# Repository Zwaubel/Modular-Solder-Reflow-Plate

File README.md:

# **Modular Solder Reflow Plate**

This project is based on [AfterEarthLTD/Solder-Reflow-Plate](https://github.com/AfterEarthLTD/Solder-Reflow-Plate) and [Johboh/Solder-Reflow-Plate](https://github.com/Johboh/Solder-Reflow-Plate)! Check out their repositories for more information.

> **⚠️ Attention:**  
> This project is currently under development and not fully tested. Building and using this project is not recommended at this time.

Changes compard to AfterEarthLTD's and Johboh's versions:
- revised main control board
  - mcu: ESP32 S3 using the WROOM module (BT and Wifi capable)
  - input voltage monitoring capabilities
  - revised component layout
  - I2C OLED display and 4-button-input
  - beeper
  - SD-Card-Reader
 
## Disclaimer
We are dealing with heat and high current here. Use at your own risk! Don't leave solder plate unattended.

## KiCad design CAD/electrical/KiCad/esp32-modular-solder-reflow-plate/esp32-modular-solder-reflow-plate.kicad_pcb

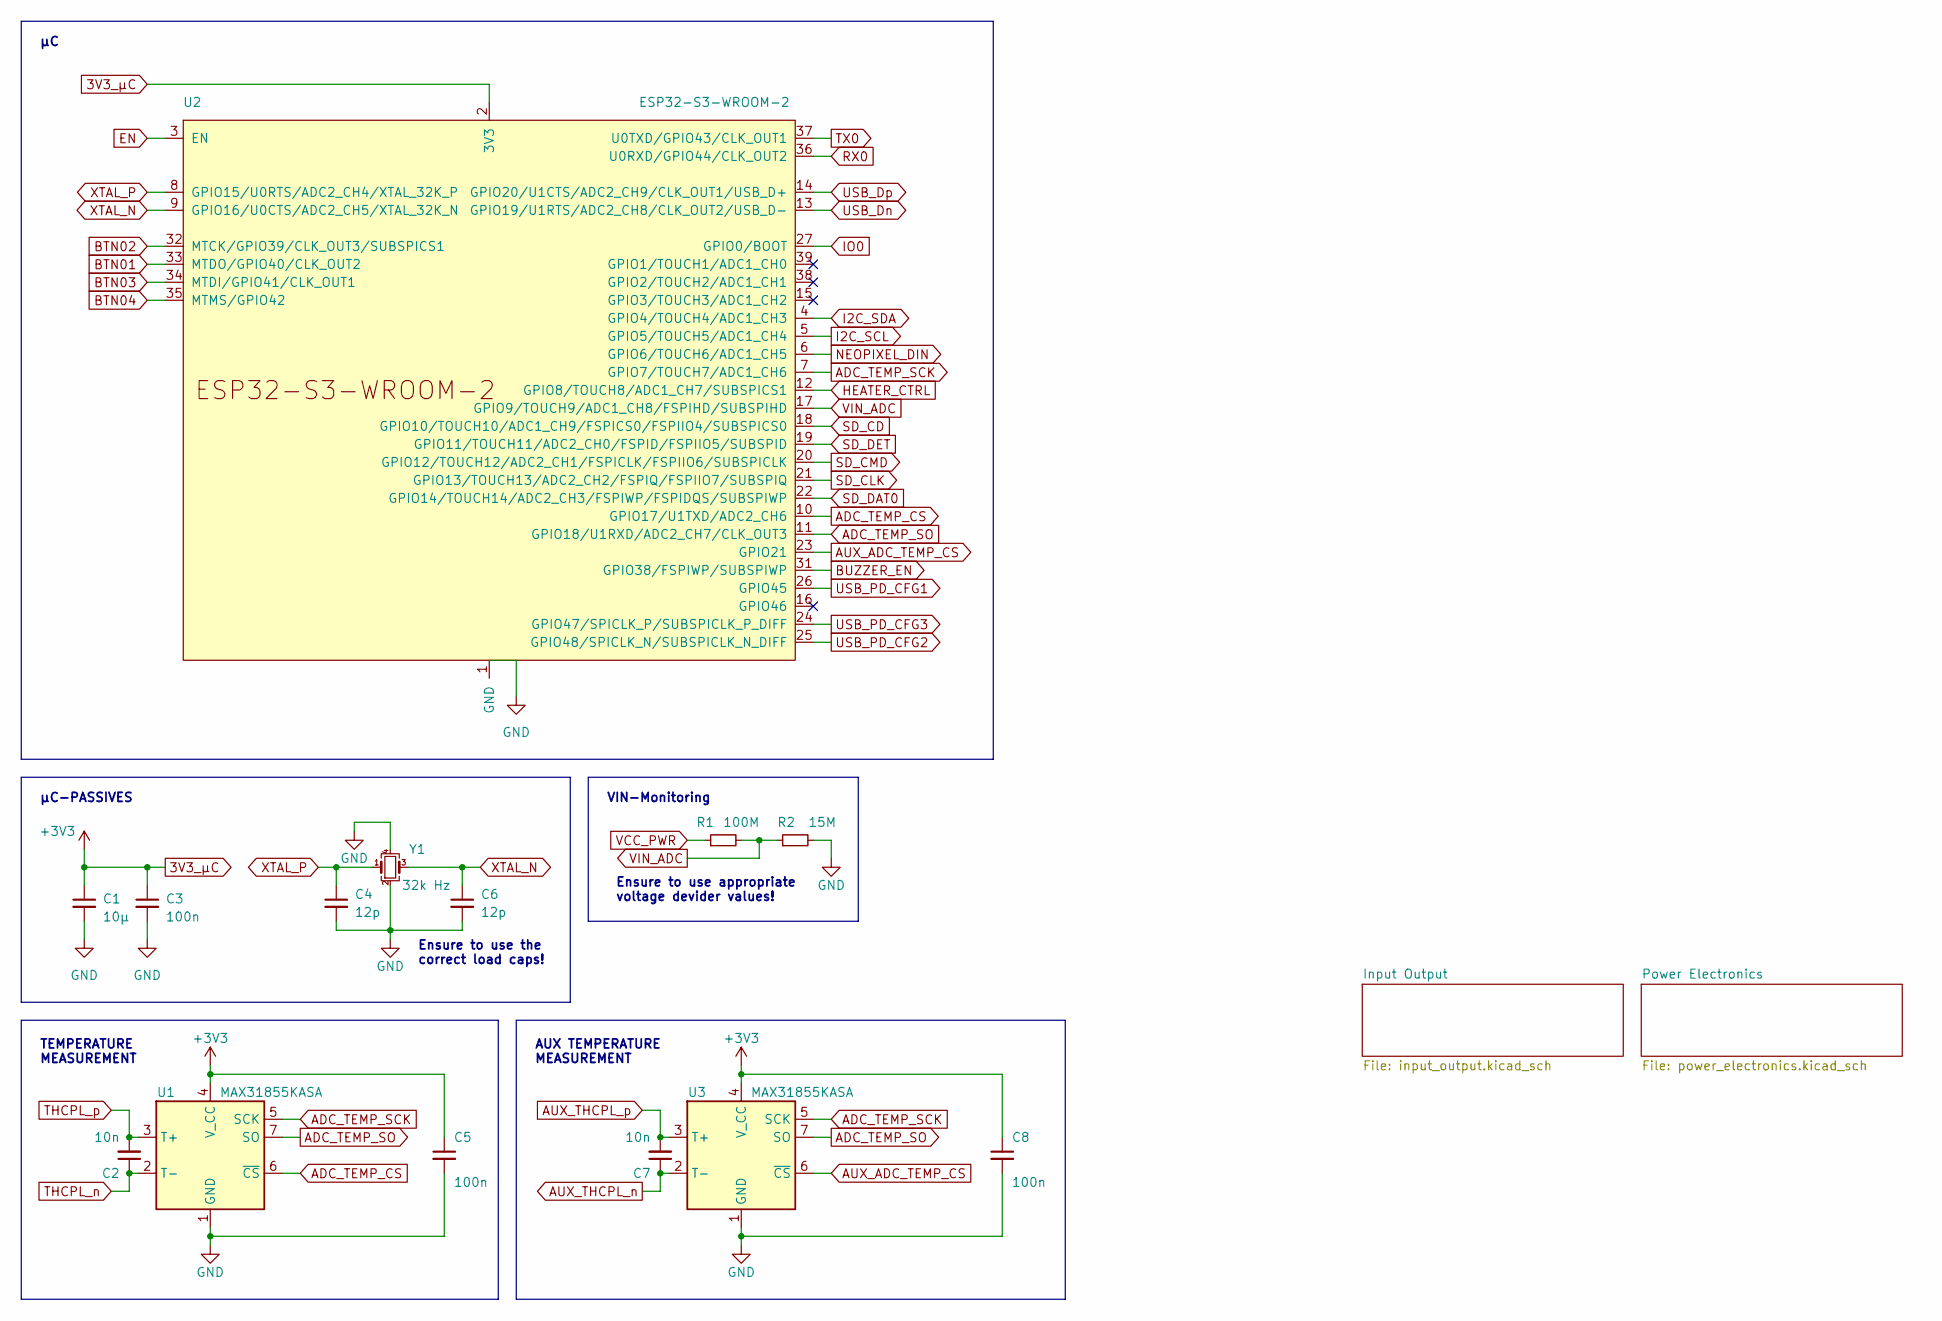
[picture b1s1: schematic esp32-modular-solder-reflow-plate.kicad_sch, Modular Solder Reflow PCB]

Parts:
C1: 10µ; C_0603_1608Metric_Pad1.08x0.95mm_HandSolder
C2, C7: 10n; C_0603_1608Metric_Pad1.08x0.95mm_HandSolder
C3, C5, C8: 100n; C_0603_1608Metric_Pad1.08x0.95mm_HandSolder
C4, C6: 12p; C_0603_1608Metric_Pad1.08x0.95mm_HandSolder
R1: 100M; R_0603_1608Metric_Pad0.98x0.95mm_HandSolder
R2: 15M; R_0603_1608Metric_Pad0.98x0.95mm_HandSolder
U1, U3: MAX31855KASA; SOIC-8_3.9x4.9mm_P1.27mm
U2: ESP32-S3-WROOM-2
Y1: 32k Hz; Crystal_SMD_3225-4Pin_3.2x2.5mm_HandSoldering

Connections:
3V3_µC: C1.1, C3.1, C5.1, C8.1, U1.4 (V_CC), U2.2 (3V3), U3.4 (V_CC); also elsewhere on the board
ADC_TEMP_CS: U1.6 (~CS), U2.10 (GPIO17/U1TXD/ADC2_CH6)
ADC_TEMP_SCK: U1.5 (SCK), U2.7 (GPIO7/TOUCH7/ADC1_CH6), U3.5 (SCK)
ADC_TEMP_SO: U1.7 (SO), U2.11 (GPIO18/U1RXD/ADC2_CH7/CLK_OUT3), U3.7 (SO)
AUX_ADC_TEMP_CS: U2.23 (GPIO21), U3.6 (~CS)
AUX_THCPL_n: C7.1, U3.2 (T-); also elsewhere on the board
AUX_THCPL_p: C7.2, U3.3 (T+); also elsewhere on the board
BTN01: U2.33 (MTDO/GPIO40/CLK_OUT2); also elsewhere on the board
BTN02: U2.32 (MTCK/GPIO39/CLK_OUT3/SUBSPICS1); also elsewhere on the board
BTN03: U2.34 (MTDI/GPIO41/CLK_OUT1); also elsewhere on the board
BTN04: U2.35 (MTMS/GPIO42); also elsewhere on the board
BUZZER_EN: U2.31 (GPIO38/FSPIWP/SUBSPIWP); also elsewhere on the board
EN: U2.3 (EN); also elsewhere on the board
HEATER_CTRL: U2.12 (GPIO8/TOUCH8/ADC1_CH7/SUBSPICS1); also elsewhere on the board
HEATER_P: R1.1; also elsewhere on the board
I2C_SCL: U2.5 (GPIO5/TOUCH5/ADC1_CH4); also elsewhere on the board
I2C_SDA: U2.4 (GPIO4/TOUCH4/ADC1_CH3); also elsewhere on the board
IO0: U2.27 (GPIO0/BOOT); also elsewhere on the board
NEOPIXEL_DIN: U2.6 (GPIO6/TOUCH6/ADC1_CH5); also elsewhere on the board
PWR_IN_N: C1.2, C3.2, C4.2, C5.2, C6.2, C8.2, R2.2, U1.1 (GND), U2.1 (GND), U2.40 (GND), U2.41 (GND), U3.1 (GND), Y1.2, Y1.4; also elsewhere on the board
RX0: U2.36 (U0RXD/GPIO44/CLK_OUT2); also elsewhere on the board
SD_CD: U2.18 (GPIO10/TOUCH10/ADC1_CH9/FSPICS0/FSPIIO4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); also elsewhere on the board
SD_CLK: U2.21 (GPIO13/TOUCH13/ADC2_CH2/FSPIQ/FSPIIO7/S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); also elsewhere on the board
SD_CMD: U2.20 (GPIO12/TOUCH12/ADC2_CH1/FSPICLK/FSPIIO6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); also elsewhere on the board
SD_DAT0: U2.22 (GPIO14/TOUCH14/ADC2_CH3/FSPIWP/FSPIDQS/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); also elsewhere on the board
SD_DET: U2.19 (GPIO11/TOUCH11/ADC2_CH0/FSPID/FSPIIO5/S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); also elsewhere on the board
THCPL_n: C2.1, U1.2 (T-); also elsewhere on the board
THCPL_p: C2.2, U1.3 (T+); also elsewhere on the board
TX0: U2.37 (U0TXD/GPIO43/CLK_OUT1); also elsewhere on the board
USB_Dn: U2.13 (GPIO19/U1RTS/ADC2_CH8/CLK_OUT2/USB_D-); also elsewhere on the board
USB_Dp: U2.14 (GPIO20/U1CTS/ADC2_CH9/CLK_OUT1/USB_D+); also elsewhere on the board
USB_PD_CFG1: U2.26 (GPIO45); also elsewhere on the board
USB_PD_CFG2: U2.25 (GPIO48/SPICLK_N/SUBSPICLK_N_DIFF); also elsewhere on the board
USB_PD_CFG3: U2.24 (GPIO47/SPICLK_P/SUBSPICLK_P_DIFF); also elsewhere on the board
VIN_ADC: R1.2, R2.1, U2.17 (GPIO9/TOUCH9/ADC1_CH8/FSPIHD/SUBSPIHD)
XTAL_N: C6.1, U2.9 (GPIO16/U0CTS/ADC2_CH5/XTAL_32K_N), Y1.3
XTAL_P: C4.1, U2.8 (GPIO15/U0RTS/ADC2_CH4/XTAL_32K_P), Y1.1

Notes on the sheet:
Ensure to use the correct load caps!
TEMPERATURE MEASUREMENT
Ensure to use appropriate voltage devider values!
µC-PASSIVES
VIN-Monitoring
AUX TEMPERATURE MEASUREMENT

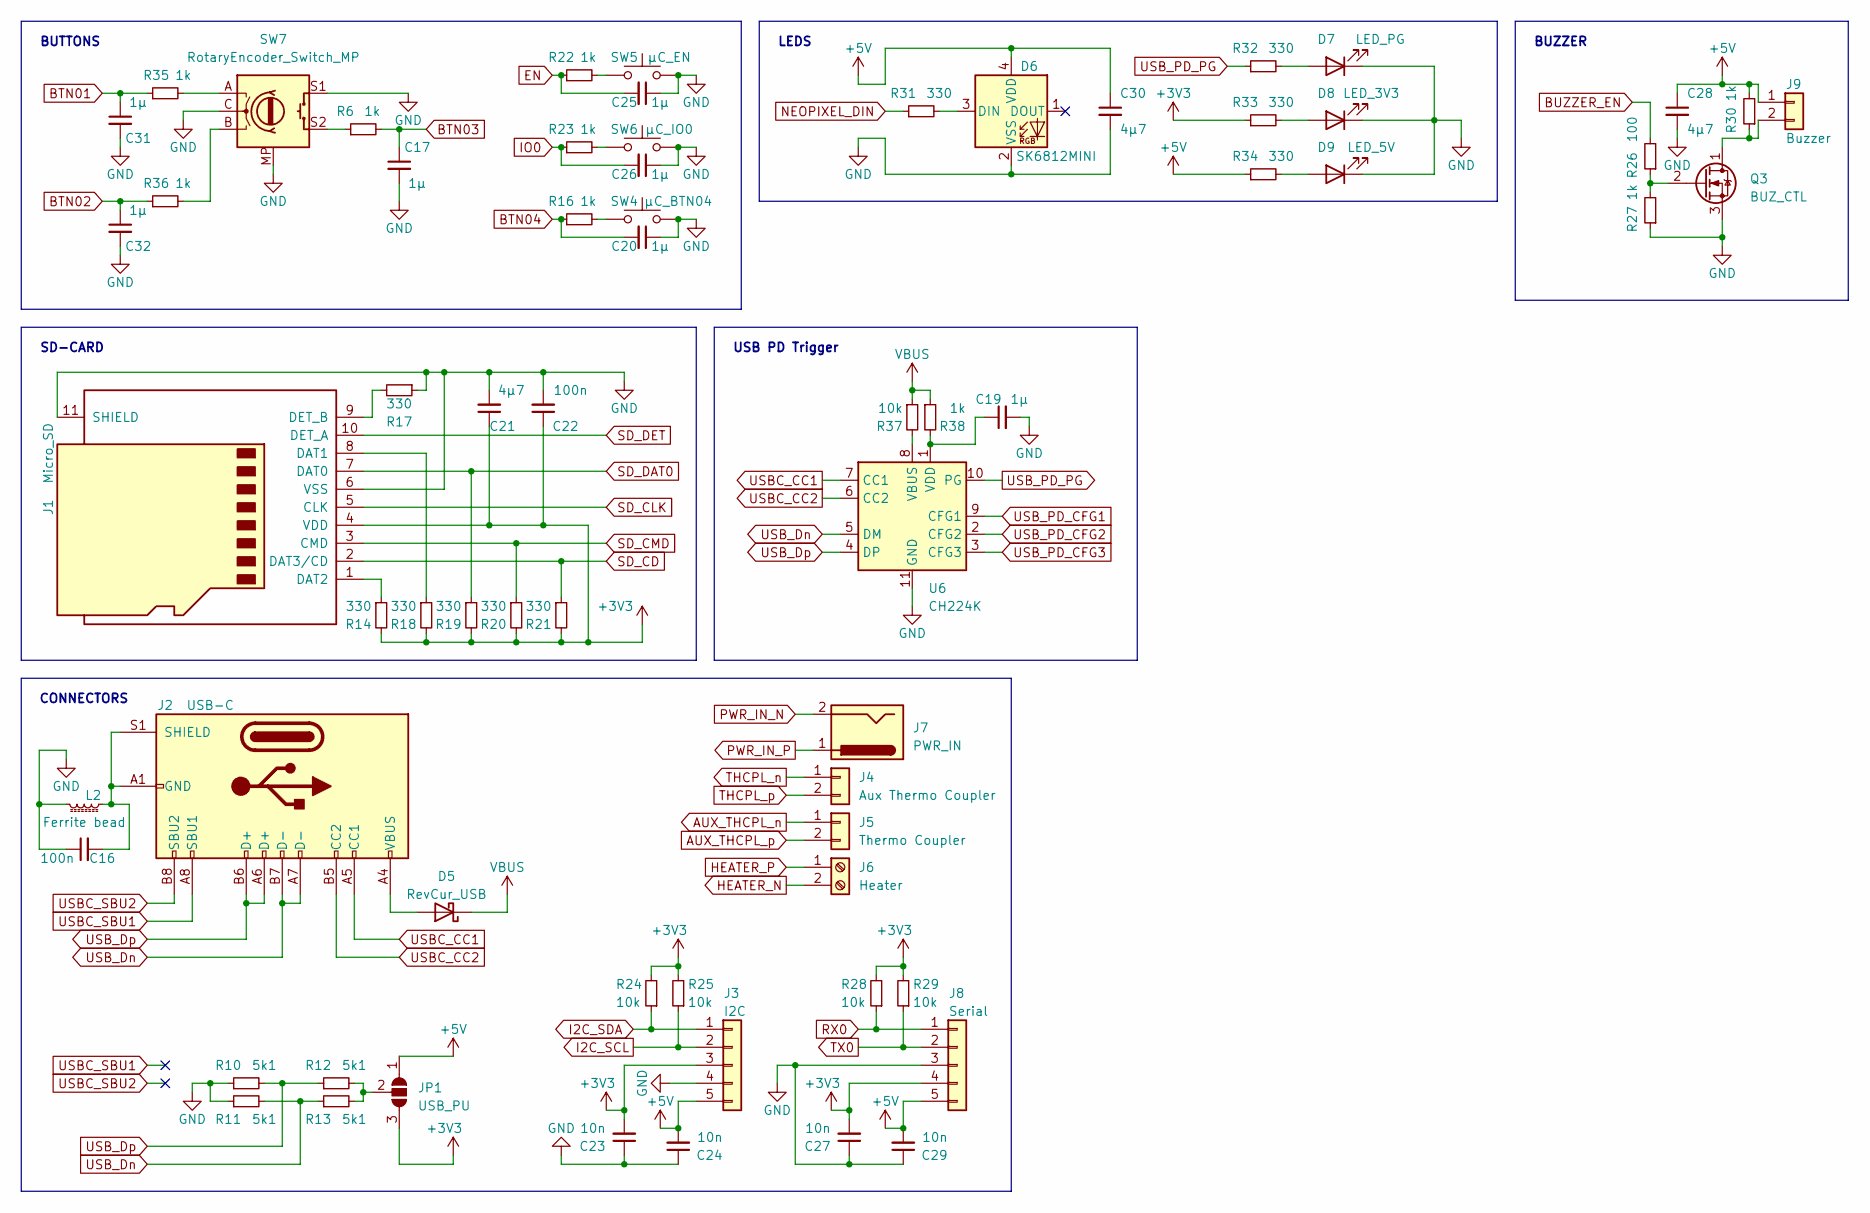
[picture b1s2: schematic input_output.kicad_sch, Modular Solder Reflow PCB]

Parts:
C16, C22: 100n; C_0603_1608Metric_Pad1.08x0.95mm_HandSolder
C17, C19, C20, C25, C26, C31, C32: 1µ; C_0603_1608Metric_Pad1.08x0.95mm_HandSolder
C21, C28, C30: 4µ7; C_0603_1608Metric_Pad1.08x0.95mm_HandSolder
C23, C24, C27, C29: 10n; C_0603_1608Metric_Pad1.08x0.95mm_HandSolder
D5: RevCur_USB; D_1210_3225Metric_Pad1.42x2.65mm_HandSolder
D6: SK6812MINI; LED_SK6812MINI_PLCC4_3.5x3.5mm_P1.75mm
D7: LED_PG; LED_0603_1608Metric_Pad1.05x0.95mm_HandSolder
D8: LED_3V3; LED_0603_1608Metric_Pad1.05x0.95mm_HandSolder
D9: LED_5V; LED_0603_1608Metric_Pad1.05x0.95mm_HandSolder
J1: Micro_SD; microSD_HC_Hirose_DM3D-SF
J2: USB-C; USB_C_Receptacle_G-Switch_GT-USB-7010ASV
J3: I2C; PinSocket_1x05_P2.54mm_Vertical
J4: Aux Thermo Coupler; JST_XH_B2B-XH-A_1x02_P2.50mm_Vertical
J5: Thermo Coupler; JST_XH_B2B-XH-A_1x02_P2.50mm_Vertical
J6: Heater; TerminalBlock_bornier-2_P5.08mm
J7: PWR_IN; BarrelJack_CUI_PJ-063AH_Horizontal
J8: Serial; PinSocket_1x05_P2.54mm_Vertical
J9: Buzzer; JST_XH_B2B-XH-A_1x02_P2.50mm_Vertical
JP1: USB_PU; SolderJumper-3_P1.3mm_Open_RoundedPad1.0x1.5mm
L2: Ferrite bead; L_0603_1608Metric_Pad1.05x0.95mm_HandSolder
Q3: BUZ_CTL; SOT-23
R6, R16, R22, R23, R27, R30, R35, R36, R38: 1k; R_0603_1608Metric_Pad0.98x0.95mm_HandSolder
R10, R11, R12, R13: 5k1; R_0603_1608Metric_Pad0.98x0.95mm_HandSolder
R14, R17, R18, R19, R20, R21, R31, R32, R33, R34: 330; R_0603_1608Metric_Pad0.98x0.95mm_HandSolder
R24, R25, R28, R29, R37: 10k; R_0603_1608Metric_Pad0.98x0.95mm_HandSolder
R26: 100; R_0603_1608Metric_Pad0.98x0.95mm_HandSolder
SW4: µC_BTN04; SW_PUSH_6mm
SW5: µC_EN; SW_Tactile_SKHH_Angled
SW6: µC_IO0; SW_Tactile_SKHH_Angled
SW7: RotaryEncoder_Switch_MP; RotaryEncoder_Alps_EC11E-Switch_Vertical_H20mm
U6: CH224K; SSOP-10-1EP_3.9x4.9mm_P1mm_EP2.1x3.3mm

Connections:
3V3_µC: C21.1, C22.1, C23.2, C27.2, J1.4 (VDD), J3.3, J8.4, JP1.3 (B), R14.2, R18.2, R19.2, R20.2, R21.2, R24.2, R25.2, R28.2, R29.2, R33.1; also elsewhere on the board
+5V: C24.2, C28.1, C29.2, C30.1, D6.4 (VDD), J3.5, J8.5, J9.1, JP1.1 (A), R30.2, R34.1; also elsewhere on the board
AUX_THCPL_n: J5.1; also elsewhere on the board
AUX_THCPL_p: J5.2; also elsewhere on the board
BTN01: C31.1, R35.1; also elsewhere on the board
BTN02: C32.1, R36.1; also elsewhere on the board
BTN03: C17.1, R6.2; also elsewhere on the board
BTN04: C20.2, R16.1; also elsewhere on the board
BUZZER_EN: R26.2; also elsewhere on the board
EN: C25.2, R22.1; also elsewhere on the board
HEATER_N: J6.2; also elsewhere on the board
HEATER_P: J6.1; also elsewhere on the board
I2C_SCL: J3.2, R25.1; also elsewhere on the board
I2C_SDA: J3.1, R24.1; also elsewhere on the board
IO0: C26.2, R23.1; also elsewhere on the board
NEOPIXEL_DIN: R31.1; also elsewhere on the board
unnamed: D5.2 (A), J2.A4 (VBUS), J2.A9 (VBUS), J2.B4 (VBUS), J2.B9 (VBUS)
unnamed: D6.3 (DIN), R31.2
unnamed: D7.2 (A), R32.2
unnamed: D8.2 (A), R33.2
unnamed: D9.2 (A), R34.2
unnamed: J1.8 (DAT1), R18.1
unnamed: J1.1 (DAT2), R14.1
unnamed: J1.9 (DET_B), R17.2
unnamed: C16.2, J2.A1 (GND), J2.A12 (GND), J2.B1 (GND), J2.B12 (GND), J2.S1 (SHIELD), L2.1
unnamed: J9.2, Q3.1 (D), R30.1
unnamed: JP1.2 (C), R12.2, R13.2
unnamed: Q3.2 (G), R26.1, R27.2
unnamed: R6.1, SW7.S2
unnamed: R16.2, SW4.1
unnamed: R22.2, SW5.1
unnamed: R23.2, SW6.1
unnamed: R35.2, SW7.A
unnamed: R36.2, SW7.B
unnamed: R37.2, U6.8 (VBUS)
unnamed: C19.1, R38.2, U6.1 (VDD)
PWR_IN_N: C16.1, C17.2, C19.2, C20.1, C21.2, C22.2, C23.1, C24.1, C25.1, C26.1, C27.1, C28.2, C29.1, C30.2, C31.2, C32.2, D6.2 (VSS), D7.1 (K), D8.1 (K), D9.1 (K), J1.6 (VSS), J1.11 (SHIELD), J3.4, J7.2, J8.3, L2.2, Q3.3 (S), R10.1, R11.1, R17.1, R27.1, SW4.2, SW5.2, SW6.2, SW7.C, SW7.MP, SW7.S1, U6.11 (GND); also elsewhere on the board
PWR_IN_P: J7.1; also elsewhere on the board
RX0: J8.1, R28.1; also elsewhere on the board
SD_CD: J1.2 (DAT3/CD), R21.1; also elsewhere on the board
SD_CLK: J1.5 (CLK); also elsewhere on the board
SD_CMD: J1.3 (CMD), R20.1; also elsewhere on the board
SD_DAT0: J1.7 (DAT0), R19.1; also elsewhere on the board
SD_DET: J1.10 (DET_A); also elsewhere on the board
THCPL_n: J4.1; also elsewhere on the board
THCPL_p: J4.2; also elsewhere on the board
TX0: J8.2, R29.1; also elsewhere on the board
USBC_CC1: J2.A5 (CC1), U6.7 (CC1)
USBC_CC2: J2.B5 (CC2), U6.6 (CC2)
USBC_SBU1: J2.A8 (SBU1)
USBC_SBU2: J2.B8 (SBU2)
USB_Dn: J2.A7 (D-), J2.B7 (D-), R11.2, R13.1, U6.5 (DM); also elsewhere on the board
USB_Dp: J2.A6 (D+), J2.B6 (D+), R10.2, R12.1, U6.4 (DP); also elsewhere on the board
USB_PD_CFG1: U6.9 (CFG1); also elsewhere on the board
USB_PD_CFG2: U6.2 (CFG2); also elsewhere on the board
USB_PD_CFG3: U6.3 (CFG3); also elsewhere on the board
USB_PD_PG: R32.1, U6.10 (PG)
VDD: D5.1 (K), R37.1, R38.1; also elsewhere on the board

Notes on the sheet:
BUZZER
BUTTONS
SD-CARD
CONNECTORS
LEDS
USB PD Trigger

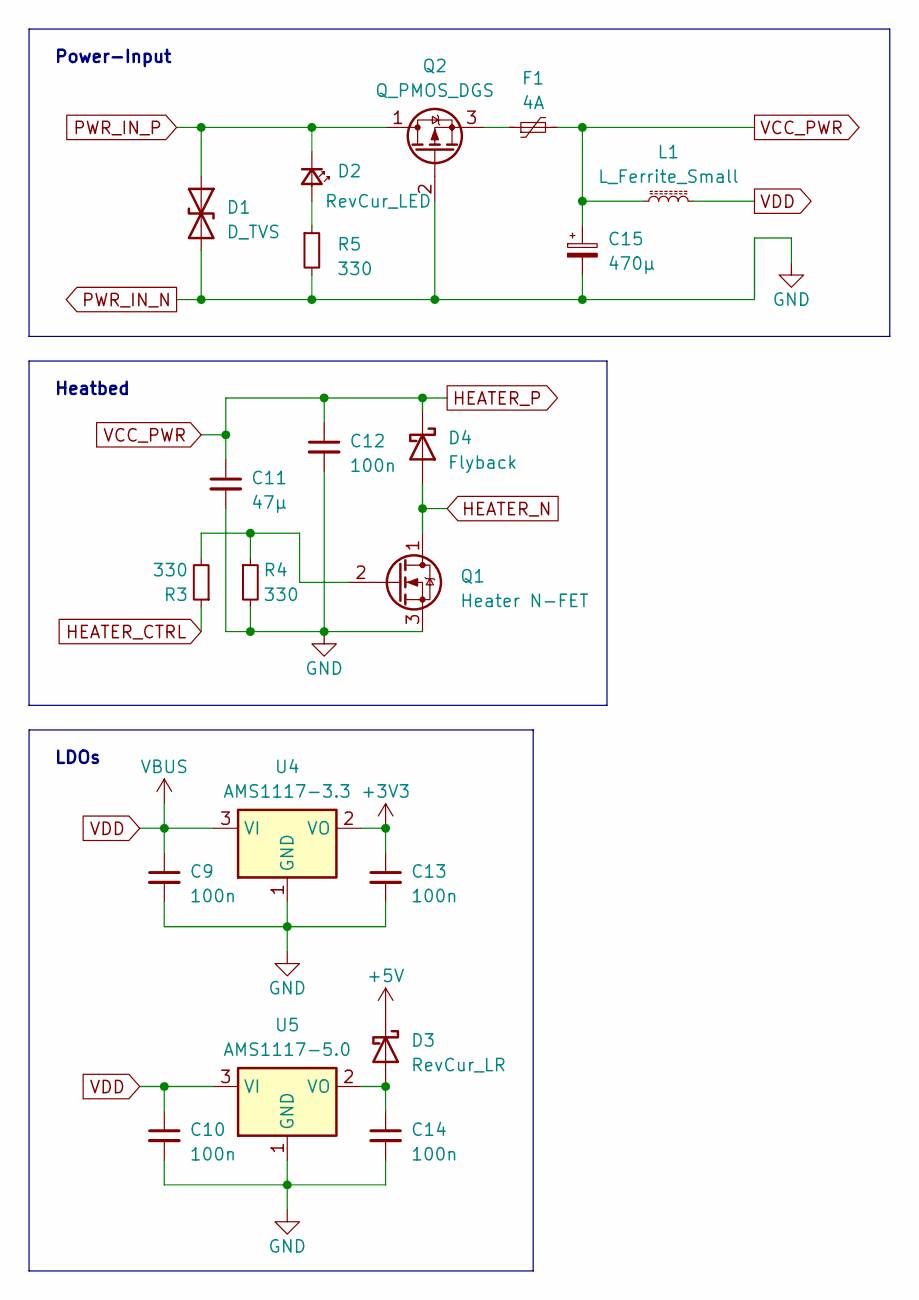
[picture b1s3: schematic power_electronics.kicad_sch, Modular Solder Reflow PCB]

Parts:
C9, C10, C12, C13, C14: 100n; C_0603_1608Metric_Pad1.08x0.95mm_HandSolder
C11: 47µ; C_0603_1608Metric_Pad1.08x0.95mm_HandSolder
C15: 470µ; CP_Radial_D6.3mm_P2.50mm
D1: D_TVS; D_0603_1608Metric_Pad1.05x0.95mm_HandSolder
D2: RevCur_LED; LED_0603_1608Metric_Pad1.05x0.95mm_HandSolder
D3: RevCur_LR; D_1210_3225Metric_Pad1.42x2.65mm_HandSolder
D4: Flyback; D_1210_3225Metric_Pad1.42x2.65mm_HandSolder
F1: 4A; Fuse_BelFuse_0ZRE0005FF_L8.3mm_W3.8mm
L1: L_Ferrite_Small; L_0805_2012Metric_Pad1.15x1.40mm_HandSolder
Q1: Heater N-FET; ATPAK-2
Q2: Q_PMOS_DGS; ATPAK-2
R3, R4, R5: 330; R_0603_1608Metric_Pad0.98x0.95mm_HandSolder
U4: AMS1117-3.3; SOT-223-3_TabPin2
U5: AMS1117-5.0; SOT-223-3_TabPin2

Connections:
3V3_µC: C13.1, U4.2 (VO); also elsewhere on the board
+5V: D3.1 (K); also elsewhere on the board
HEATER_CTRL: R3.1; also elsewhere on the board
HEATER_N: D4.2 (A), Q1.1 (D); also elsewhere on the board
HEATER_P: C11.1, C12.1, C15.1, D4.1 (K), F1.2, L1.1; also elsewhere on the board
unnamed: D2.2 (A), R5.1
unnamed: C14.1, D3.2 (A), U5.2 (VO)
unnamed: Q1.2 (G), R3.2, R4.1
unnamed: F1.1, Q2.3 (S)
PWR_IN_N: C9.2, C10.2, C11.2, C12.2, C13.2, C14.2, C15.2, D1.2 (A2), Q1.3 (S), Q2.2 (G), R4.2, R5.2, U4.1 (GND), U5.1 (GND); also elsewhere on the board
PWR_IN_P: D1.1 (A1), D2.1 (K), Q2.1 (D); also elsewhere on the board
VDD: C9.1, C10.1, L1.2, U4.3 (VI), U5.3 (VI); also elsewhere on the board

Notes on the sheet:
Power-Input
Heatbed
LDOs

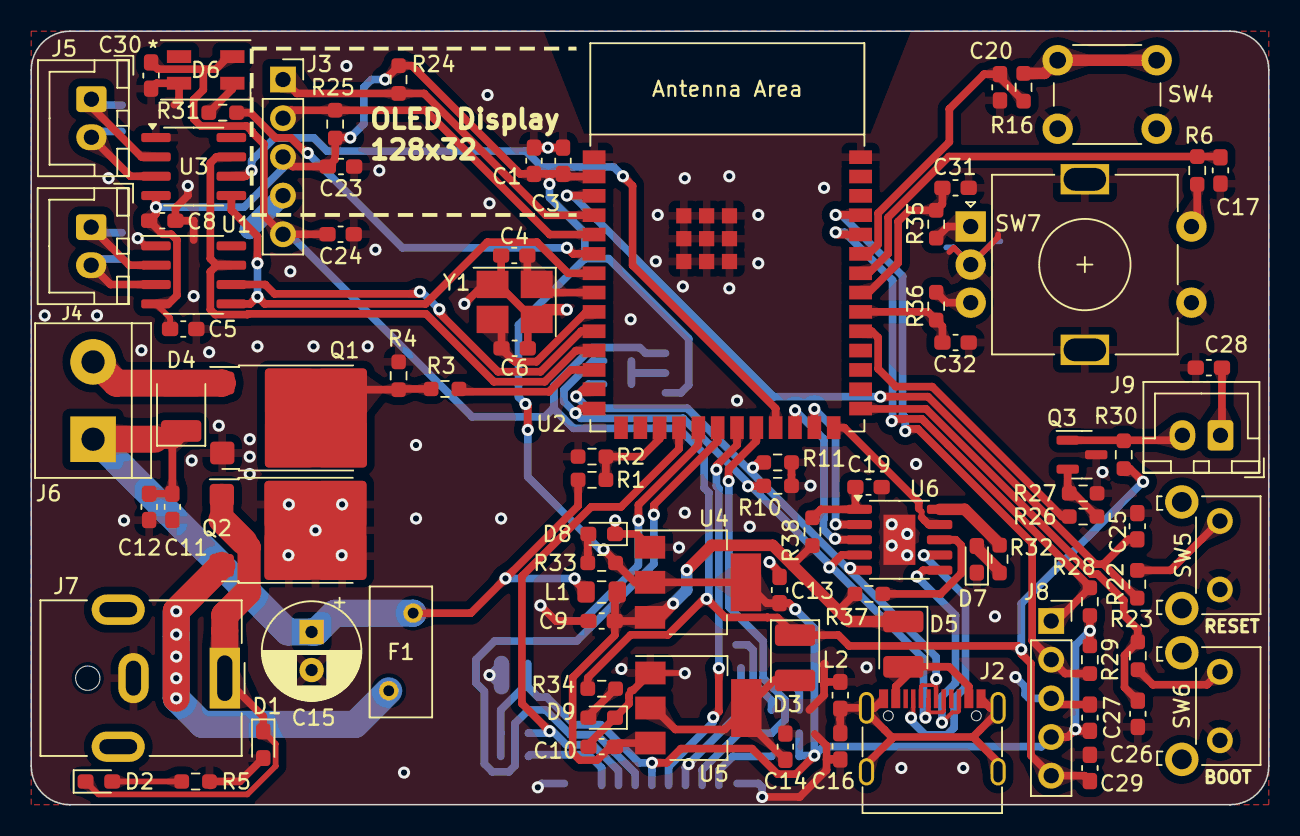
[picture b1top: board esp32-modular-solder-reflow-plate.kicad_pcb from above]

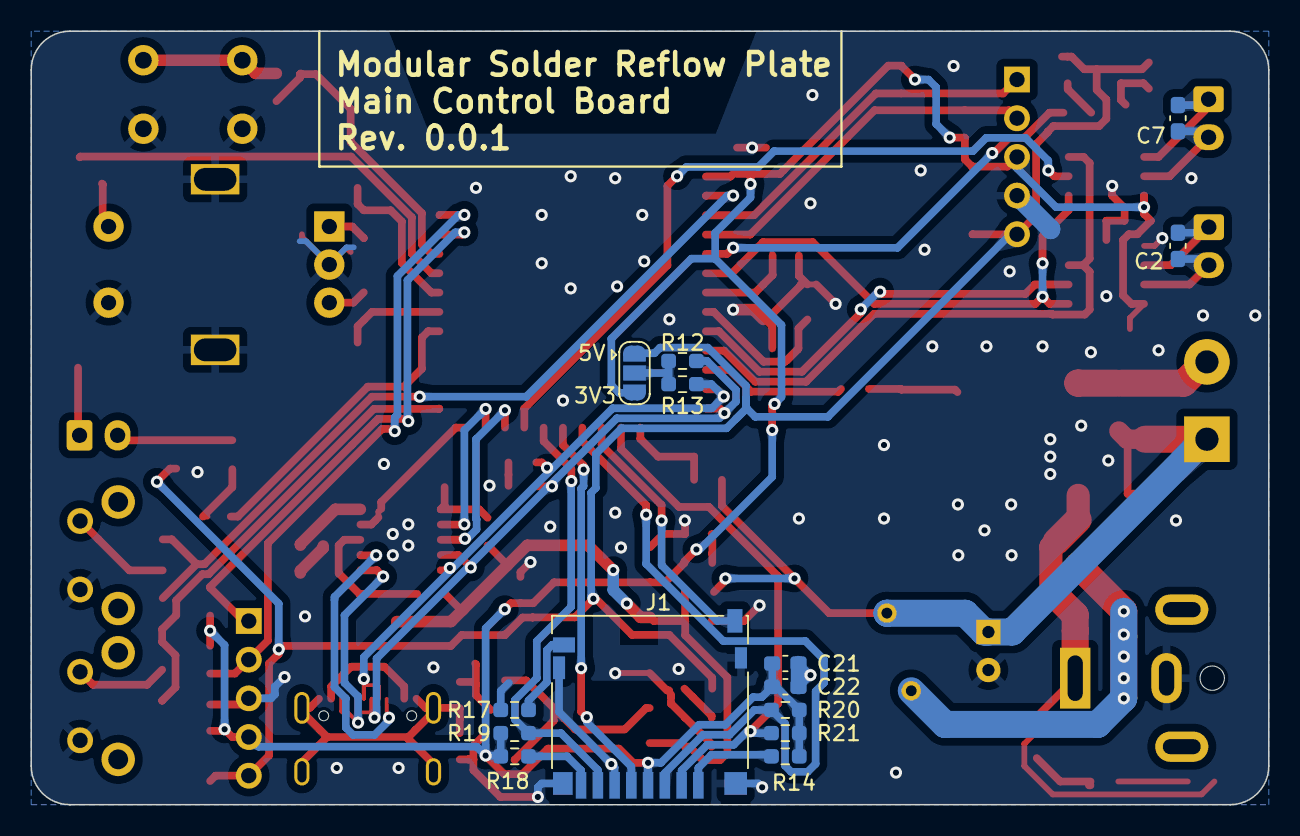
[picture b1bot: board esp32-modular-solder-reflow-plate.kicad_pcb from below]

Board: 2 copper layers, 81.3 x 50.8 mm, 101 parts (14 on the bottom side), 68 nets.

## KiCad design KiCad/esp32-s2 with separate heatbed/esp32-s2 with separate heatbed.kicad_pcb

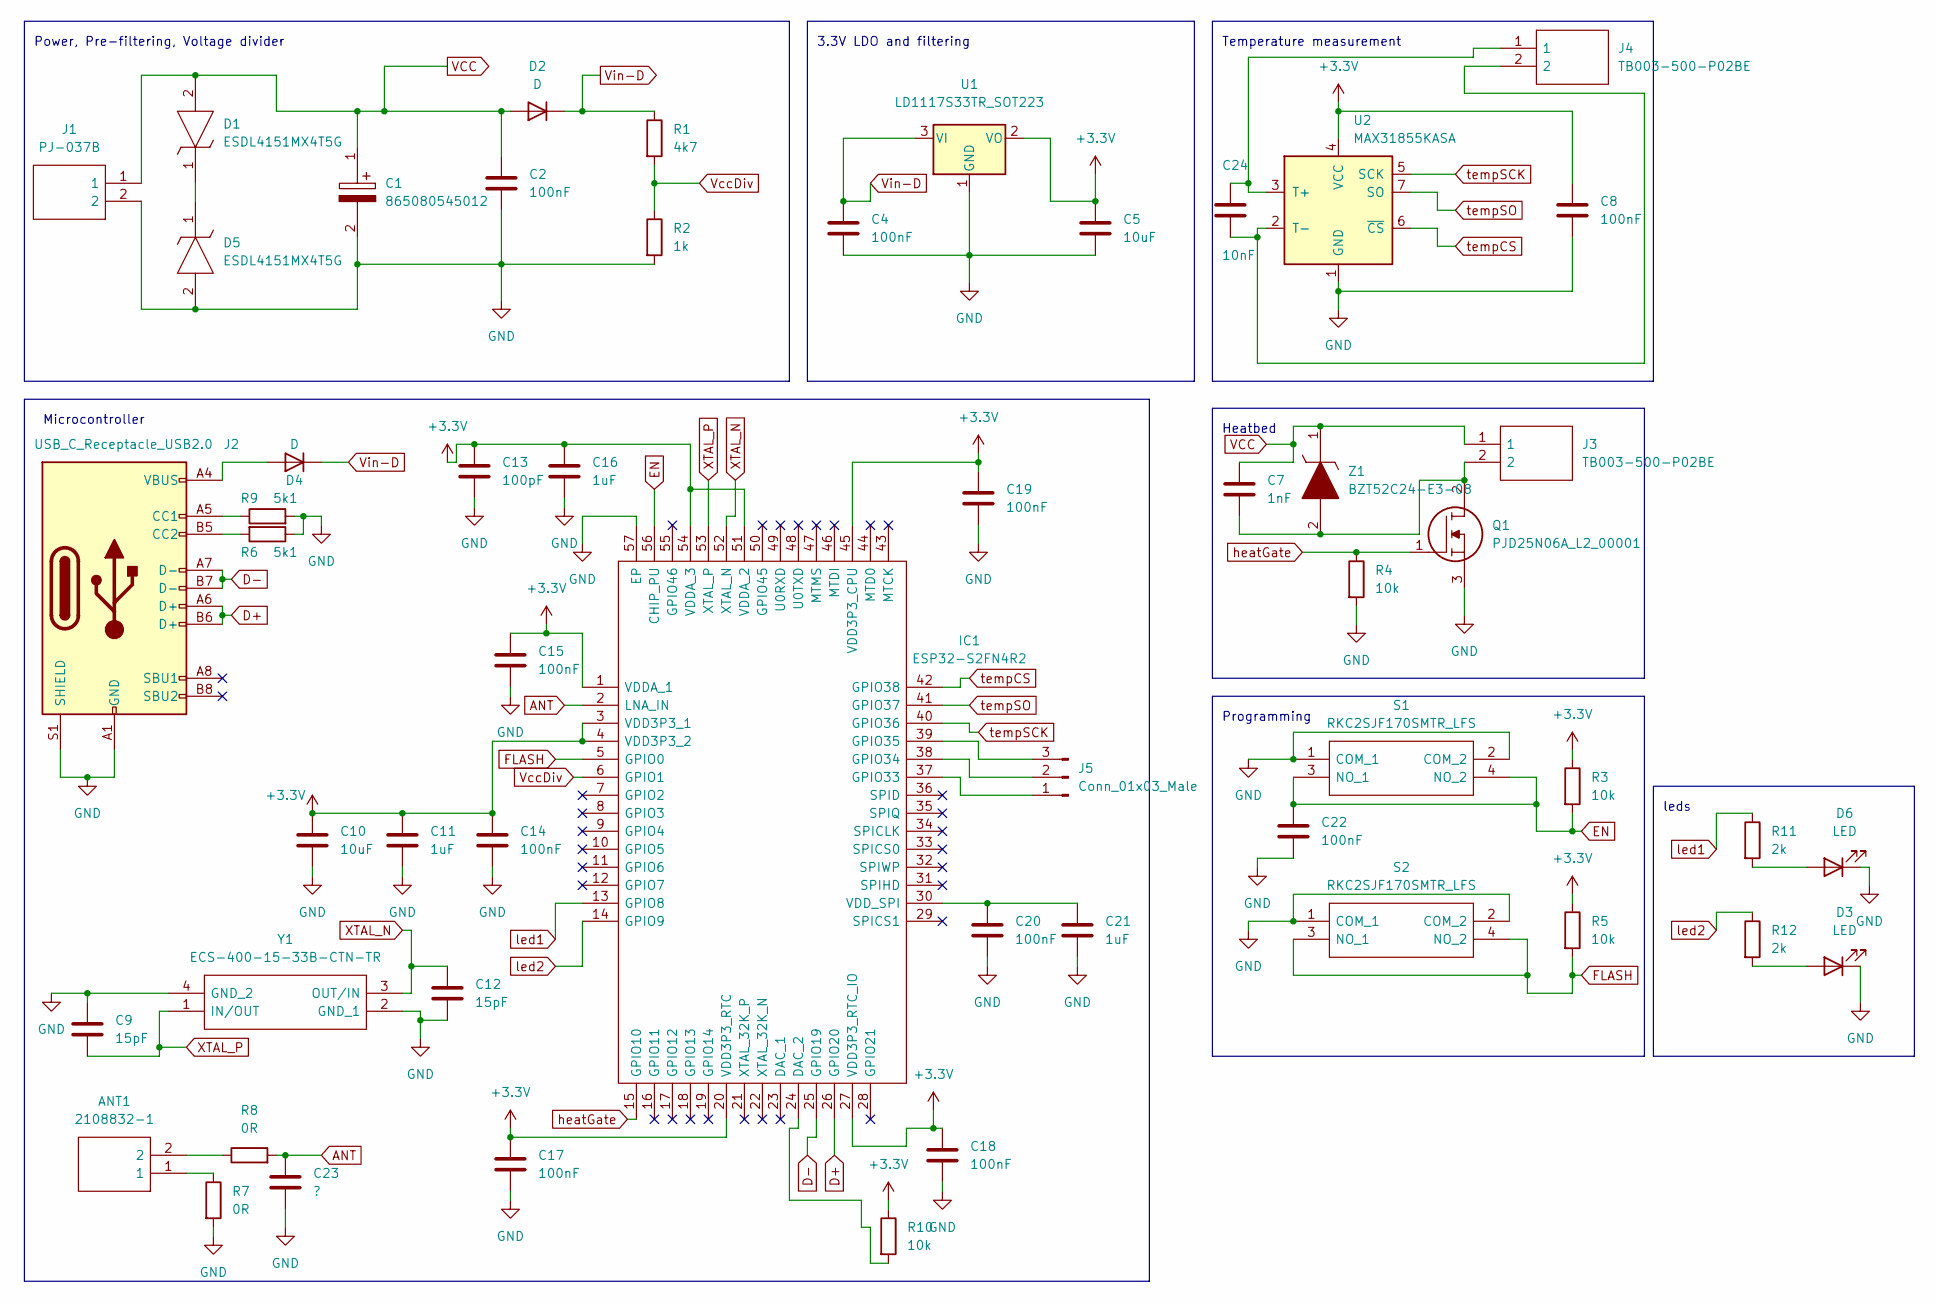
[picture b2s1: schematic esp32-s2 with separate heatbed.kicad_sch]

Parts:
ANT1: 2108832-1; 21088321; Manufacturer_Part_Number 2108832-1
C1: 865080545012; CAPAE660X770N; Mouser Part Number 710-865080545012
C2, C4, C8, C14, C15, C17, C18, C19, C20, C22: 100nF; C_0603_1608Metric
C5, C10: 10uF; C_0603_1608Metric
C7: 1nF; C_0805_2012Metric
C9, C12: 15pF; C_0603_1608Metric
C11, C16, C21: 1uF; C_0603_1608Metric
C13: 100pF; C_0603_1608Metric
C23: ?; C_0603_1608Metric
C24: 10nF; C_0603_1608Metric
D1, D5: ESDL4151MX4T5G; Mouser Part Number 863-ESDL4151MX4T5G
D2, D4: D; D_SOD-123
D3, D6: LED; D_0603_1608Metric
IC1: ESP32-S2FN4R2; QFN40P700X700X90-57N-D; Mouser Part Number 356-ESP32-S2FN4R2
J1: PJ-037B; PJ037B; Mouser Part Number 490-PJ-037B
J2: USB_C_Receptacle_USB2.0; TYPE-C-31-M-12
J3, J4: TB003-500-P02BE; SHDR2W100P0X500_1X2_1000X780X1030P; Mouser Part Number 490-TB003-500-P02BE
J5: Conn_01x03_Male; PinHeader_1x03_P2.54mm_Vertical
Q1: PJD25N06A_L2_00001; Mouser Part Number 241-PJD25N06AL200001
R1: 4k7; R_0603_1608Metric
R2: 1k; R_0603_1608Metric
R3, R4, R5, R10: 10k; R_0603_1608Metric
R6, R9: 5k1; R_0603_1608Metric
R7, R8: 0R; R_0603_1608Metric
R11, R12: 2k; R_0603_1608Metric
S1, S2: RKC2SJF170SMTR_LFS; RKC2SJF170SMTRLFS; Mouser Part Number 611-RKC2SJF170SMRLFS
U1: LD1117S33TR_SOT223; SOT-223-3_TabPin2
U2: MAX31855KASA; SOIC-8_3.9x4.9mm_P1.27mm
Y1: ECS-400-15-33B-CTN-TR; ECS2501033BCKMTR; Mouser Part Number 520-400-15-33B-CTNT
Z1: BZT52C24-E3-08; BZT52C24E308; Mouser Part Number 78-BZT52C24-E3-08

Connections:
+3V3: C5.1, C8.1, C10.1, C11.1, C13.1, C14.1, C15.1, C16.1, C17.1, C18.1, C19.1, IC1.1 (VDDA_1), IC1.3 (VDD3P3_1), IC1.4 (VDD3P3_2), IC1.20 (VDD3P3_RTC), IC1.27 (VDD3P3_RTC_IO), IC1.45 (VDD3P3_CPU), IC1.51 (VDDA_2), IC1.54 (VDDA_3), R3.1, R5.1, R10.1, U1.2 (VO), U2.4 (VCC)
ANT: C23.1, IC1.2 (LNA_IN), R8.2
D+: IC1.26 (GPIO20), J2.A6 (D+), J2.B6 (D+)
D-: IC1.25 (GPIO19), J2.A7 (D-), J2.B7 (D-)
EN: C22.1, IC1.56 (CHIP_PU), R3.2, S1.3 (NO_1), S1.4 (NO_2)
FLASH: IC1.5 (GPIO0), R5.2, S2.3 (NO_1), S2.4 (NO_2)
GND: C1.2, C2.2, C4.2, C5.2, C8.2, C9.1, C10.2, C11.2, C12.2, C13.2, C14.2, C15.2, C16.2, C17.2, C18.2, C19.2, C20.2, C21.2, C22.2, C23.2, D3.1 (K), D5.2, D6.1 (K), IC1.57 (EP), J1.2, J2.A1 (GND), J2.A12 (GND), J2.B1 (GND), J2.B12 (GND), J2.S1 (SHIELD), Q1.3, R2.2, R4.2, R6.1, R7.2, R9.2, S1.1 (COM_1), S1.2 (COM_2), S2.1 (COM_1), S2.2 (COM_2), U1.1 (GND), U2.1 (GND), Y1.2 (GND_1), Y1.4 (GND_2)
unnamed: ANT1.1, R7.1
unnamed: ANT1.2, R8.1
unnamed: C7.2, J3.2, Q1.2, Z1.2
unnamed: C20.1, C21.1, IC1.30 (VDD_SPI)
unnamed: C24.1, J4.1, U2.3 (T+)
unnamed: C24.2, J4.2, U2.2 (T-)
unnamed: D1.1, D5.1
unnamed: D3.2 (A), R12.2
unnamed: D4.2 (A), J2.A4 (VBUS), J2.A9 (VBUS), J2.B4 (VBUS), J2.B9 (VBUS)
unnamed: D6.2 (A), R11.2
unnamed: IC1.24 (DAC_2), R10.2
unnamed: IC1.37 (GPIO33), J5.1
unnamed: IC1.38 (GPIO34), J5.2
unnamed: IC1.39 (GPIO35), J5.3
unnamed: J2.B5 (CC2), R6.2
unnamed: J2.A5 (CC1), R9.1
VCC: C1.1, C2.1, C7.1, D1.2, D2.2 (A), J1.1, J3.1, Z1.1
VccDiv: IC1.6 (GPIO1), R1.2, R2.1
Vin-D: C4.1, D2.1 (K), D4.1 (K), R1.1, U1.3 (VI)
XTAL_N: C12.1, IC1.52 (XTAL_N), Y1.3 (OUT/IN)
XTAL_P: C9.2, IC1.53 (XTAL_P), Y1.1 (IN/OUT)
heatGate: IC1.15 (GPIO10), Q1.1, R4.1
led1: IC1.13 (GPIO8), R11.1
led2: IC1.14 (GPIO9), R12.1
tempCS: IC1.42 (GPIO38), U2.6 (~CS)
tempSCK: IC1.40 (GPIO36), U2.5 (SCK)
tempSO: IC1.41 (GPIO37), U2.7 (SO)

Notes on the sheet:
Heatbed
Temperature measurement
Power, Pre-filtering, Voltage divider
leds
Programming
Microcontroller
3.3V LDO and filtering

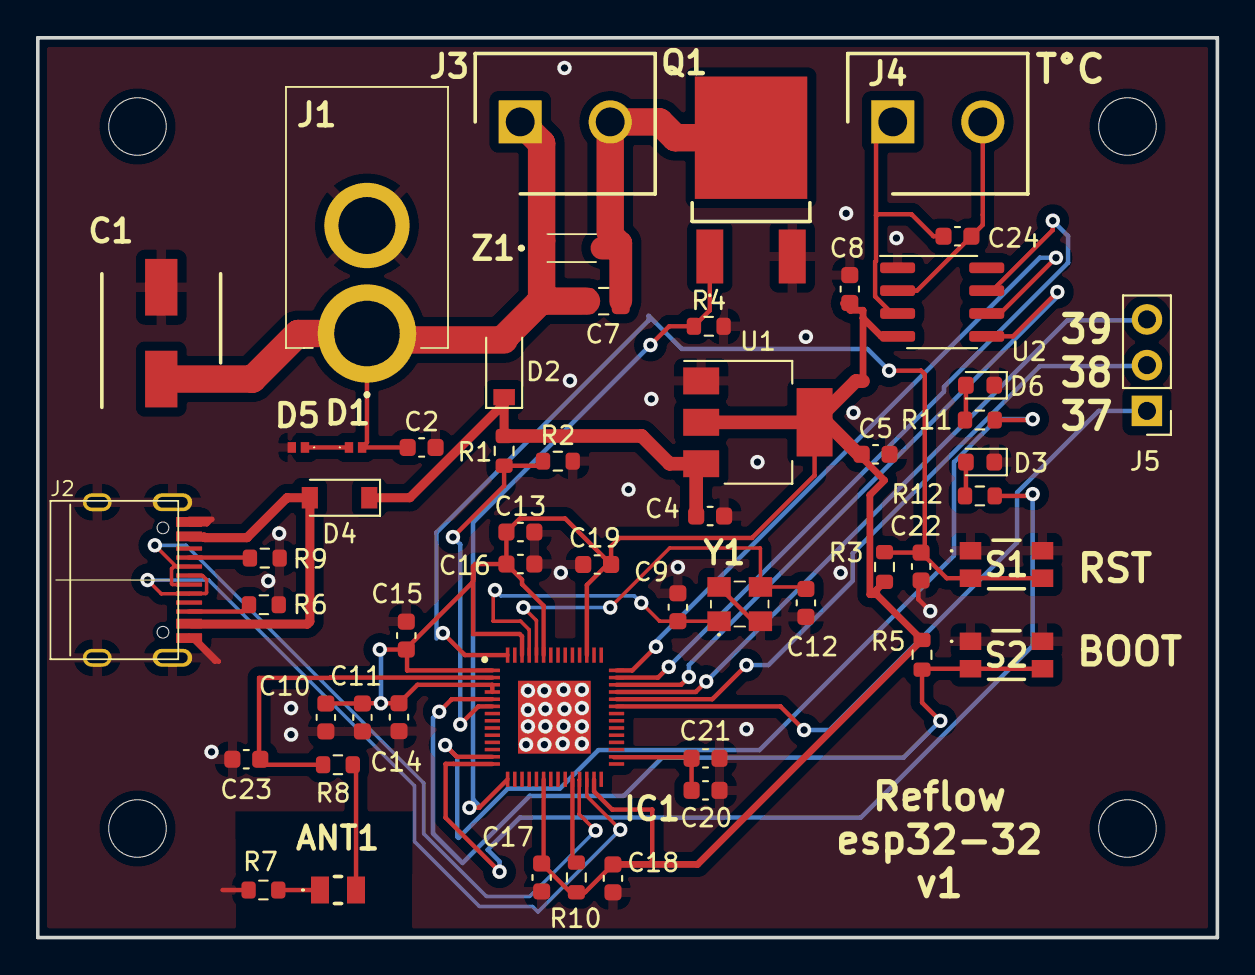
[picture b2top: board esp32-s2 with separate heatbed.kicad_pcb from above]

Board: 2 copper layers, 65.5 x 50.0 mm, 54 parts (0 on the bottom side), 34 nets.

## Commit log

2022-03-09 Initial in progress esp8266 schematic
2022-03-09 LDO + temperature
2022-03-09 Add library loader
2022-03-09 Some more that I don't remember
2022-03-09 Switches
2022-03-09 Use relative paths for models
2022-03-09 Rename from esp8266 -> Esp32-s2 (as this is the new arch)
2022-03-09 Move gitignore up to kicad folder
2022-03-09 Add esp32-s2, not routed
2022-03-09 Add tactile switches
2022-03-09 Microcontrolling schematics, not complete
2022-03-10 Add Antenna + mosfet + connectors
2022-03-10 Back diode for USB vbus
2022-03-12 Vdd SPI no 3.3V, and add capacitor for EN
2022-03-12 Footprints and connect esp32 peripherals
2022-03-12 Add leds (and other things I don't remember)
2022-03-12 Inital PCB
2022-03-14 Routing complete
2022-03-15 Add C for antenna
2022-03-15 Move antenna to edge
2022-03-15 Add heatbed
2022-03-15 Corrections
2022-03-15 New mounting holes
2022-03-15 Spacing
2022-03-15 Add BOM
2022-03-15 Replace wrong USB-C with a correct one
2022-03-15 Higher resistance heatbed
2022-03-26 Add software init test
    Verifying that esp32, leds, wifi works
2022-03-26 Add Thermocouple test
2022-03-26 Switch max31855 library
2022-03-27 Split into classes
2022-03-27 Add controller and other voltage out
2022-03-27 Call correct function in setup
2022-03-27 Add duty Serial control
2022-03-27 Add some documentation/todo to controller
2022-03-27 Add Remote integration, only publish for now
2022-03-27 Update name of credentials
2022-03-27 Expose duty cycle
2022-03-27 Update boom
2022-03-27 Add reflow on/off (toggle) as well as profile selector to HA
2022-03-27 Rename heatbed to 70x50 and indicate Resistance, and add 80x60 heatbed with 1.6R
2022-03-27 Add missing caution
2022-03-28 Correct resistance for heatbed 1.6
2022-03-28 Remove original version/documentation, as these are better viewed upstream
2022-03-29 Name nets
2022-03-29 Add bottom silk screen
2022-03-30 Add non routed 95x95 board
2022-03-30 Route 95x95mm board
2022-03-31 5% increments
2022-03-31 Fix include path
2022-03-31 Flatten the structure
2022-03-31 Add mising reference for library
2022-03-31 Add some initial profile handling, draft
2022-04-01 Profile logic and states (a lot of stuff in one commit here)
2022-04-01 Add heater
2022-04-01 Some pre-PID work
2022-04-01 Somewhat smooter reflow graph
2022-04-01 Start Y from previous target value
2022-04-02 Quick release on low temp.
2022-04-02 Publish target temperature
2022-04-02 Remove cooling state. Same as idle.
2022-04-02 Add PID reference
2022-04-02 Cleanup and documentation
2022-04-04 Move library loader into project folder to use relative paths
2022-04-08 Remove non functional heatbeds (too high resistance)
2022-04-09 Add note about core version
2022-04-20 Set value for D2/D4 and add note about C23 and LED resistors
2022-04-20 Support different max duty cycle per board type, and work with percentages instead of raw duty cycle
2022-04-20 Move aggressiveness factor to profile
2022-04-20 Publish setup less frequently
2022-04-20 Adjust profile for 80x60mm board
2022-11-19 Add some more logging around profie selection
2022-11-19 More profile logging
2023-03-21 - CAD: initial KiCad project rework with espressif kicad lib as a submodule and µC swapped with esp32 s3 wroom
2023-03-23 - CAD: schematic improvements
2023-04-12 - CAD: remove proprietary lib
2023-04-12 - CAD: remove obsolete bom
2023-04-12 - CAD: initial routed pcb
2023-04-16 - CAD: pcb routing improvements
2023-04-16 - CAD: library clean up, routing improvements, new heat bed terminal
2023-04-20 - cad: added USB d+ and d- pull up and pull down options; optimized overall component layout; improved silkscreens
2023-04-21 - firmware: converted arduino sketch to vscode platformio project
2023-04-21 - cad: restructurer folderrs
2023-04-22 - firmware: revise source file structure
2023-04-22 Update README.md
    - readme: mention both AfterEarthLTD and Johboh
2023-04-22 Update README.md
    - readme: fix mcu
2023-04-22 - cad: improved routing; added VIN voltage monitoring capability
2023-04-22 - cad: swapped WS2812 against SK6812Mini
2023-04-22 - cad: added a buzzer control output
2023-04-22 - firmware: added buzzer ctl pin definition
2023-04-22 - readme: document card reader
2023-04-22 - cad: minor routing improvements
2023-04-26 - cad: routing and silkscreen improvements
2023-04-26 - cad: added bypass cap for the buzzer
2023-04-27 - cad: fixed usb c sbu pins; improved usb c slot routing
2023-04-27 - cad: fix deprecated files
2023-04-27 - cad: beautify the schematic
2023-04-27 - firmware: add HAL to enable different platforms by adding HAL definitions
2023-04-29 - firmware: add recommended cpptools plugin and set platform framework version
2023-04-29 - cad: update espressif lib submodule
2024-02-09 - code: update firmware
2024-02-13 - cad: add an auxiliary temperature probe input
2024-08-20 - libs: update espressif lib
2024-11-19 - CAD: added usb pd trigger configurable via esp, routing adjustments
2025-05-19 - docs: note that the project is still under development
